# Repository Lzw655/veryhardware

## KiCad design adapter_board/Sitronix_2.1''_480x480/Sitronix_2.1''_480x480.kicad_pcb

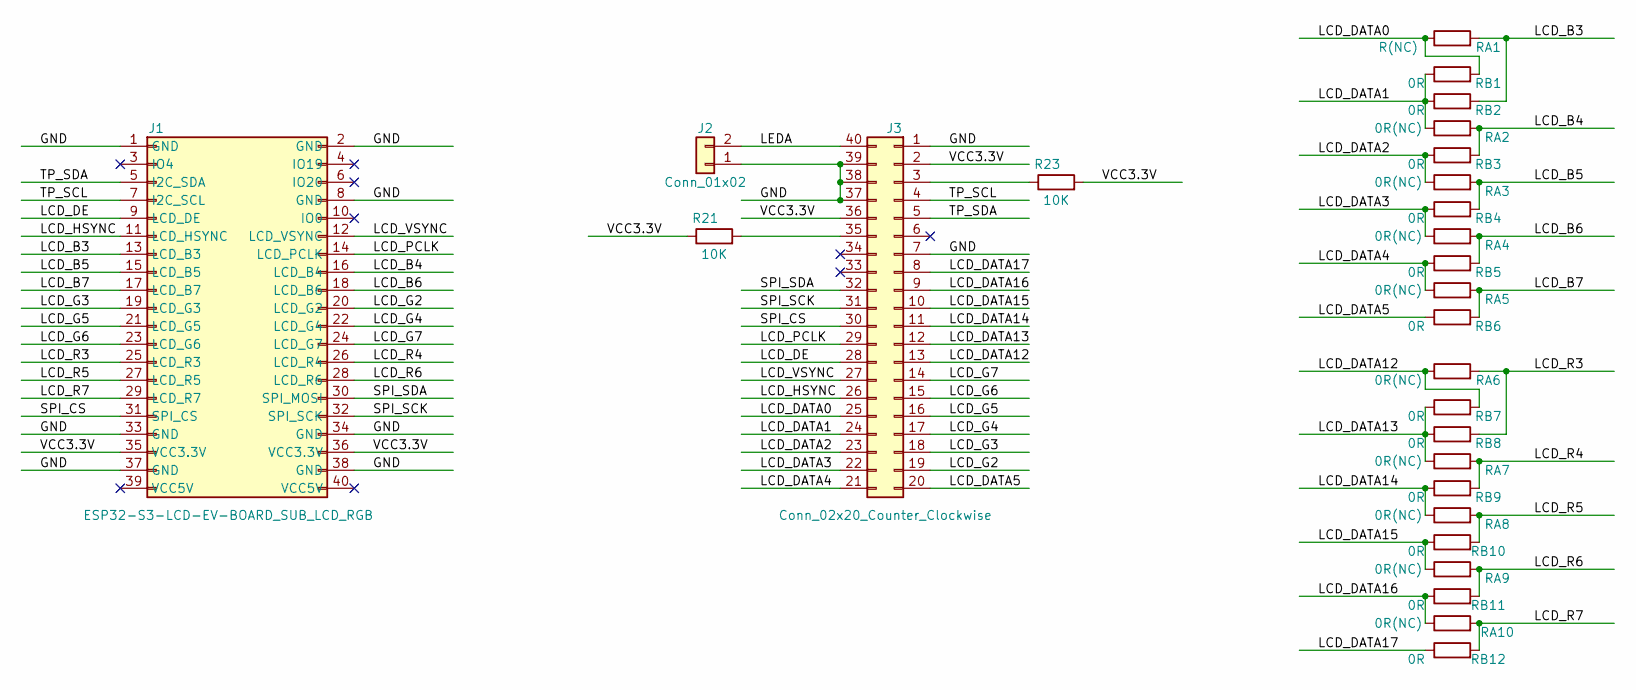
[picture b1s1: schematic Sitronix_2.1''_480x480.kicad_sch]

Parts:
J1: ESP32-S3-LCD-EV-BOARD_SUB_LCD_RGB
J2: Conn_01x02; PinHeader_1x02_P2.54mm_Vertical
J3: Conn_02x20_Counter_Clockwise; Hirose_FH12-40S-0.5SH_1x40-1MP_P0.50mm_Horizontal
R21, R23: 10K; R_0402_1005Metric
RA1, RA2, RA3, RA4, RA5, RA6, RA7, RA8, RA9, RA10: 0R(NC); R_0402_1005Metric
RB1, RB2, RB3, RB4, RB5, RB6, RB7, RB8, RB9, RB10, RB11, RB12: 0R; R_0402_1005Metric

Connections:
/GND: J1.1 (GND), J1.2 (GND), J1.8 (GND), J1.33 (GND), J1.34 (GND), J1.37 (GND), J1.38 (GND), J2.1, J3.1, J3.7, J3.37, J3.38, J3.39, J3.MP
/LCD_B3: J1.13 (LCD_B3), RA1.2, RB2.2
/LCD_B4: J1.16 (LCD_B4), RA2.2, RB3.2
/LCD_B5: J1.15 (LCD_B5), RA3.2, RB4.2
/LCD_B6: J1.18 (LCD_B6), RA4.2, RB5.2
/LCD_B7: J1.17 (LCD_B7), RA5.2, RB6.2
/LCD_DATA0: J3.25, RA1.1, RB1.2
/LCD_DATA1: J3.24, RA2.1, RB1.1, RB2.1
/LCD_DATA2: J3.23, RA3.1, RB3.1
/LCD_DATA3: J3.22, RA4.1, RB4.1
/LCD_DATA4: J3.21, RA5.1, RB5.1
/LCD_DATA5: J3.20, RB6.1
/LCD_DATA12: J3.13, RA6.1, RB7.2
/LCD_DATA13: J3.12, RA7.1, RB7.1, RB8.1
/LCD_DATA14: J3.11, RA8.1, RB9.1
/LCD_DATA15: J3.10, RA9.1, RB10.1
/LCD_DATA16: J3.9, RA10.1, RB11.1
/LCD_DATA17: J3.8, RB12.1
/LCD_DE: J1.9 (LCD_DE), J3.28
/LCD_G2: J1.20 (LCD_G2), J3.19
/LCD_G3: J1.19 (LCD_G3), J3.18
/LCD_G4: J1.22 (LCD_G4), J3.17
/LCD_G5: J1.21 (LCD_G5), J3.16
/LCD_G6: J1.23 (LCD_G6), J3.15
/LCD_G7: J1.24 (LCD_G7), J3.14
/LCD_HSYNC: J1.11 (LCD_HSYNC), J3.26
/LCD_PCLK: J1.14 (LCD_PCLK), J3.29
/LCD_R3: J1.25 (LCD_R3), RA6.2, RB8.2
/LCD_R4: J1.26 (LCD_R4), RA7.2, RB9.2
/LCD_R5: J1.27 (LCD_R5), RA8.2, RB10.2
/LCD_R6: J1.28 (LCD_R6), RA9.2, RB11.2
/LCD_R7: J1.29 (LCD_R7), RA10.2, RB12.2
/LCD_VSYNC: J1.12 (LCD_VSYNC), J3.27
/LEDA: J2.2, J3.40
/SPI_CS: J1.31 (SPI_CS), J3.30
/SPI_SCK: J1.32 (SPI_SCK), J3.31
/SPI_SDA: J1.30 (SPI_MOSI), J3.32
/TP_SCL: J1.7 (I2C_SCL), J3.4
/TP_SDA: J1.5 (I2C_SDA), J3.5
/VCC3.3V: J1.35 (VCC3.3V), J1.36 (VCC3.3V), J3.2, J3.36, R21.1, R23.2
unnamed: J3.3, R23.1
unnamed: J3.35, R21.2

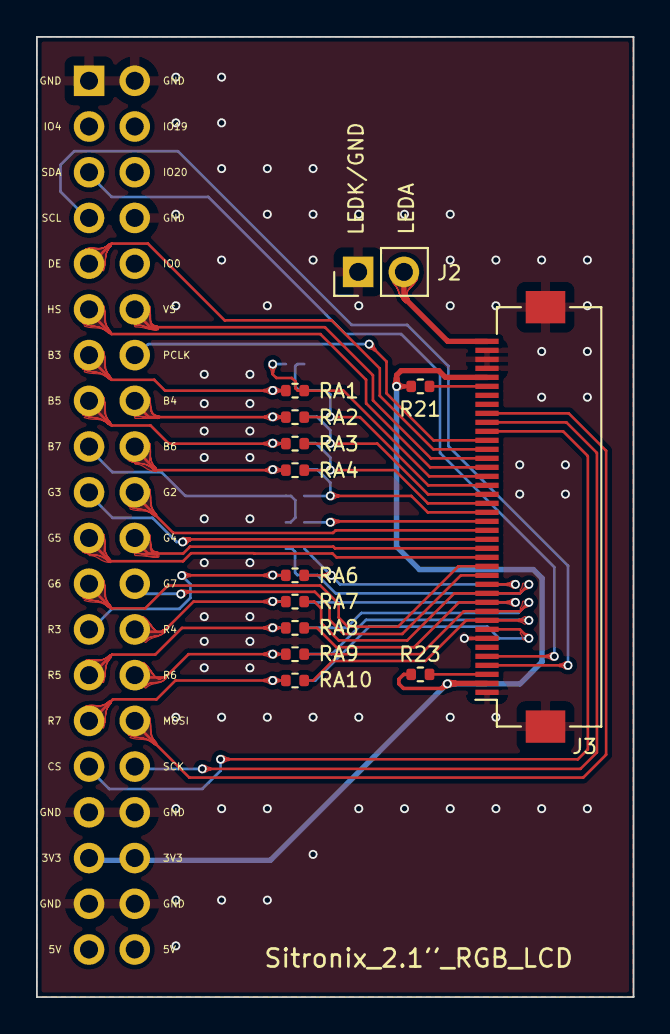
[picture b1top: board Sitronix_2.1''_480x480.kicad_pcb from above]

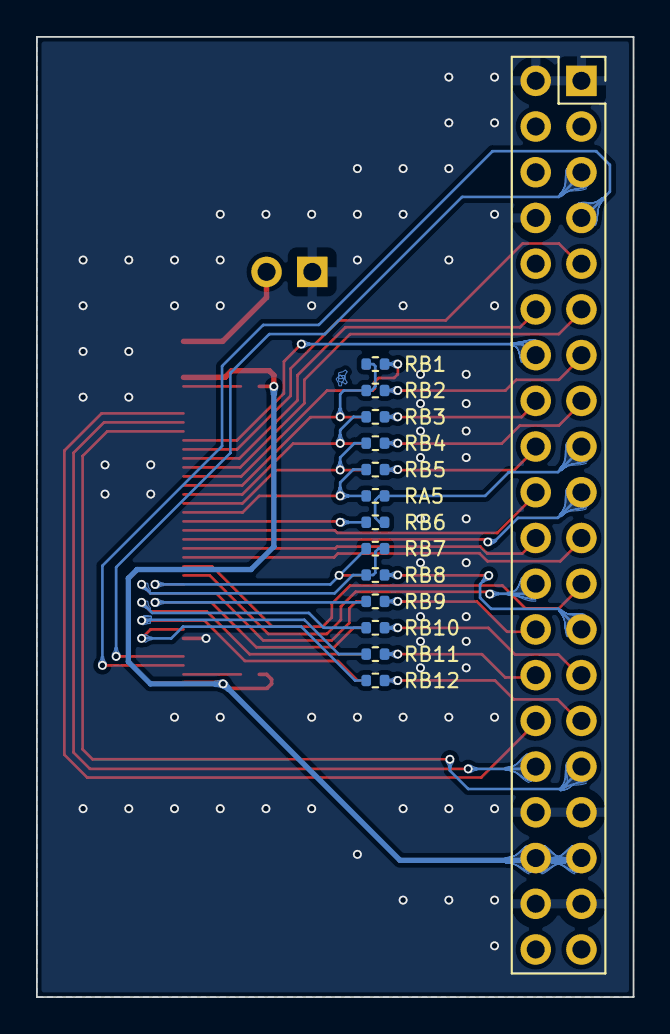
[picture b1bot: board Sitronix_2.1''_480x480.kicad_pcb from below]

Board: 2 copper layers, 33.1 x 53.3 mm, 27 parts (13 on the bottom side), 42 nets.

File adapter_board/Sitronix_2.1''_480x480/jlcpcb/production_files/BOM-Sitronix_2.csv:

Comment,Designator,Footprint,LCSC
ESP32-S3-LCD-EV-BOARD_SUB_LCD_RGB,J1,ESP32-S3-LCD-EV-BOARD_SUB_LCD_RGB,
0R(NC),RA10,R_0402_1005Metric,
10K,R23,R_0402_1005Metric,
0R(NC),RA8,R_0402_1005Metric,
R(NC),RA1,R_0402_1005Metric,
Conn_01x02,J2,PinHeader_1x02_P2.54mm_Vertical,
0R(NC),RA7,R_0402_1005Metric,
10K,R21,R_0402_1005Metric,
0R(NC),RA9,R_0402_1005Metric,
Conn_02x20_Counter_Clockwise,J3,Hirose_FH12-40S-0.5SH_1x40-1MP_P0.50mm_Horizontal,
0R(NC),RA4,R_0402_1005Metric,
0R(NC),RA2,R_0402_1005Metric,
0R(NC),RA3,R_0402_1005Metric,
0R(NC),RA6,R_0402_1005Metric,
0R,RB7,R_0402_1005Metric,
0R,RB2,R_0402_1005Metric,
0R,RB1,R_0402_1005Metric,
0R,RB9,R_0402_1005Metric,
0R,RB5,R_0402_1005Metric,
0R,RB12,R_0402_1005Metric,
0R,RB4,R_0402_1005Metric,
0R,RB8,R_0402_1005Metric,
0R,RB6,R_0402_1005Metric,
0R(NC),RA5,R_0402_1005Metric,
0R,RB11,R_0402_1005Metric,
0R,RB10,R_0402_1005Metric,
0R,RB3,R_0402_1005Metric,

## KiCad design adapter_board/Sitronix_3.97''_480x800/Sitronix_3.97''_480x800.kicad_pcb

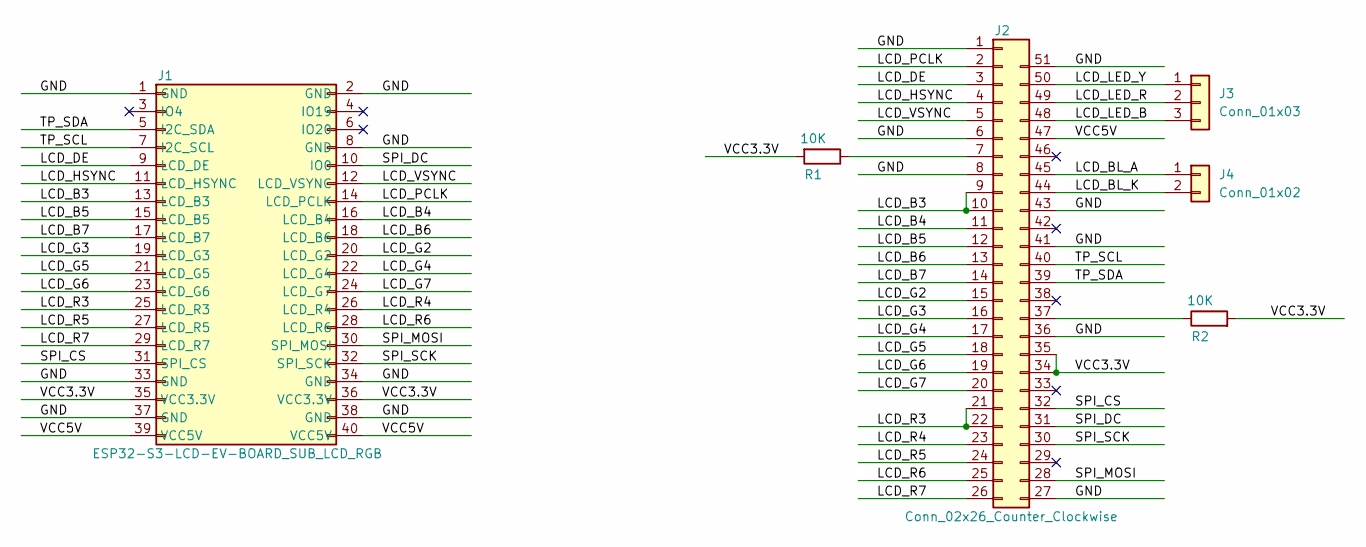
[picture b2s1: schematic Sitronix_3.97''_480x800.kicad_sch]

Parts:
J1: ESP32-S3-LCD-EV-BOARD_SUB_LCD_RGB; PinSocket_2x20_P2.54mm_Vertical
J2: Conn_02x26_Counter_Clockwise; Molex_502250-5191_2Rows-51Pins-1MP_P0.60mm_Horizontal
J3: Conn_01x03; PinHeader_1x03_P2.54mm_Vertical
J4: Conn_01x02; PinHeader_1x02_P2.54mm_Vertical
R1, R2: 10K; R_0603_1608Metric

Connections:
/GND: J1.1 (GND), J1.2 (GND), J1.8 (GND), J1.33 (GND), J1.34 (GND), J1.37 (GND), J1.38 (GND), J2.1, J2.6, J2.8, J2.27, J2.36, J2.41, J2.43, J2.51
/LCD_B3: J1.13 (LCD_B3), J2.9, J2.10
/LCD_B4: J1.16 (LCD_B4), J2.11
/LCD_B5: J1.15 (LCD_B5), J2.12
/LCD_B6: J1.18 (LCD_B6), J2.13
/LCD_B7: J1.17 (LCD_B7), J2.14
/LCD_BL_A: J2.45, J4.1
/LCD_BL_K: J2.44, J4.2
/LCD_DE: J1.9 (LCD_DE), J2.3
/LCD_G2: J1.20 (LCD_G2), J2.15
/LCD_G3: J1.19 (LCD_G3), J2.16
/LCD_G4: J1.22 (LCD_G4), J2.17
/LCD_G5: J1.21 (LCD_G5), J2.18
/LCD_G6: J1.23 (LCD_G6), J2.19
/LCD_G7: J1.24 (LCD_G7), J2.20
/LCD_HSYNC: J1.11 (LCD_HSYNC), J2.4
/LCD_LED_B: J2.48, J3.3
/LCD_LED_R: J2.49, J3.2
/LCD_LED_Y: J2.50, J3.1
/LCD_PCLK: J1.14 (LCD_PCLK), J2.2
/LCD_R3: J1.25 (LCD_R3), J2.21, J2.22
/LCD_R4: J1.26 (LCD_R4), J2.23
/LCD_R5: J1.27 (LCD_R5), J2.24
/LCD_R6: J1.28 (LCD_R6), J2.25
/LCD_R7: J1.29 (LCD_R7), J2.26
/LCD_VSYNC: J1.12 (LCD_VSYNC), J2.5
/SPI_CS: J1.31 (SPI_CS), J2.32
/SPI_DC: J1.10 (IO0), J2.31
/SPI_MOSI: J1.30 (SPI_MOSI), J2.28
/SPI_SCK: J1.32 (SPI_SCK), J2.30
/TP_SCL: J1.7 (I2C_SCL), J2.40
/TP_SDA: J1.5 (I2C_SDA), J2.39
/VCC3.3V: J1.35 (VCC3.3V), J1.36 (VCC3.3V), J2.34, J2.35, R1.2, R2.2
/VCC5V: J1.39 (VCC5V), J1.40 (VCC5V), J2.47
unnamed: J2.7, R1.1
unnamed: J2.37, R2.1

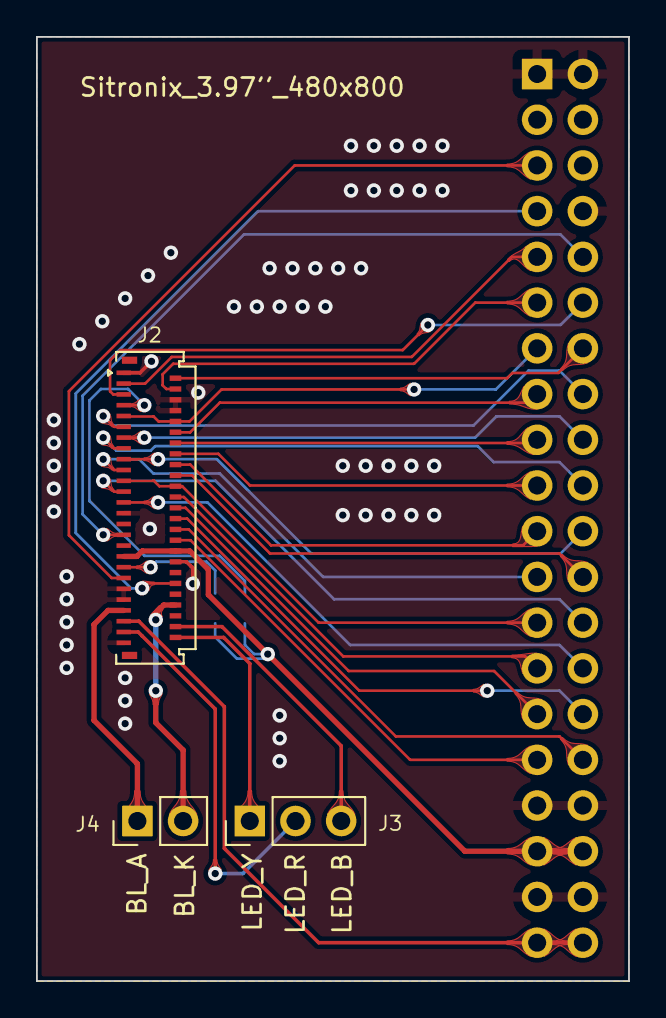
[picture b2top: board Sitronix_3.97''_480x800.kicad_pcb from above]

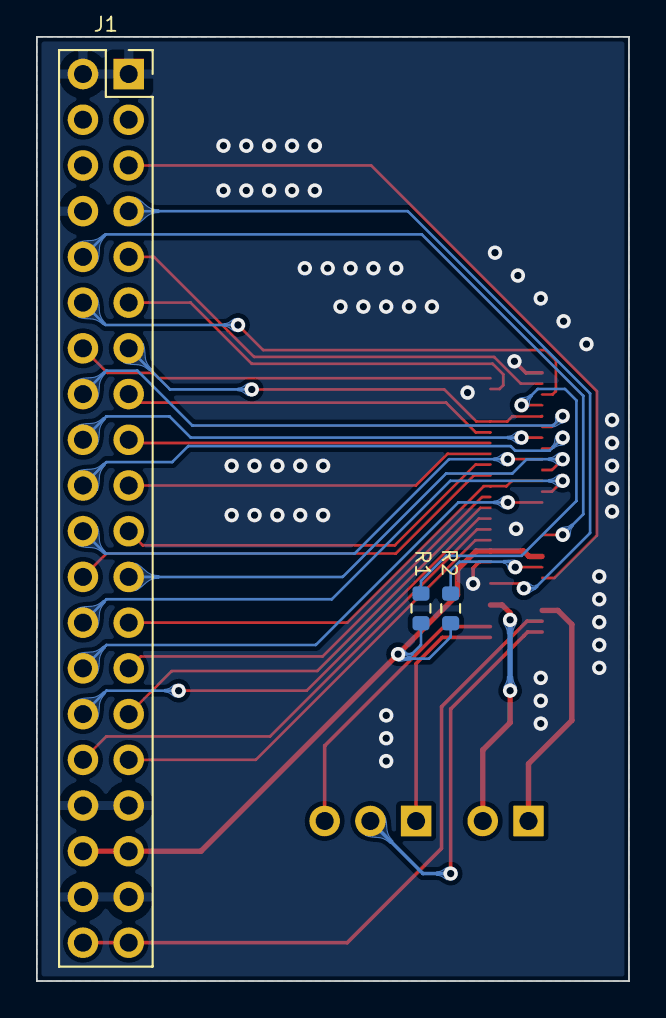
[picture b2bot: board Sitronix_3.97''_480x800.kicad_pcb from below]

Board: 2 copper layers, 32.9 x 52.5 mm, 6 parts (3 on the bottom side), 36 nets.

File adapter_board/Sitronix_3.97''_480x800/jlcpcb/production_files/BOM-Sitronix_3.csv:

Comment,Designator,Footprint,LCSC
Conn_02x26_Counter_Clockwise,J2,Molex_502250-5191_2Rows-51Pins-1MP_P0.60mm_Horizontal,
10K,R2,R_0603_1608Metric,
Conn_01x02,J4,PinHeader_1x02_P2.54mm_Vertical,
Conn_01x03,J3,PinHeader_1x03_P2.54mm_Vertical,
10K,R1,R_0603_1608Metric,
ESP32-S3-LCD-EV-BOARD_SUB_LCD_RGB,J1,PinSocket_2x20_P2.54mm_Vertical,

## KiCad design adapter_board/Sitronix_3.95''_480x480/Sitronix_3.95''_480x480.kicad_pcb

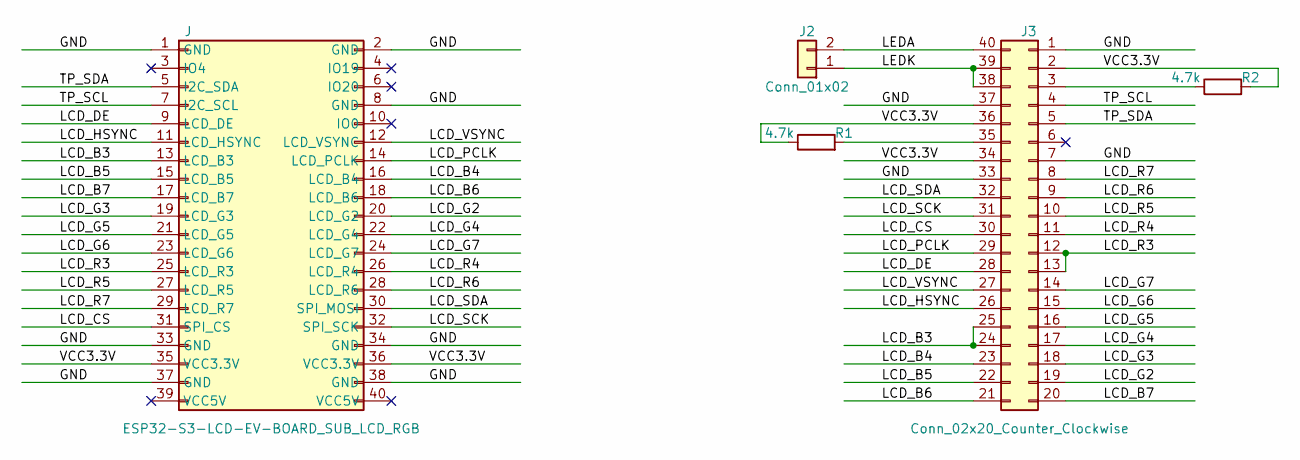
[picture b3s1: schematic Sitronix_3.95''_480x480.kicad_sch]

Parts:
J: ESP32-S3-LCD-EV-BOARD_SUB_LCD_RGB; PinSocket_2x20_P2.54mm_Vertical
J2: Conn_01x02
J3: Conn_02x20_Counter_Clockwise
R1: 4.7k
R2: 4.7k; R_0603_1608Metric

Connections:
/GND: J.1 (GND), J.2 (GND), J.8 (GND), J.33 (GND), J.34 (GND), J.37 (GND), J.38 (GND), J3.1, J3.7, J3.33, J3.37, J3.MP
/LCD_B3: J.13 (LCD_B3), J3.24, J3.25
/LCD_B4: J.16 (LCD_B4), J3.23
/LCD_B5: J.15 (LCD_B5), J3.22
/LCD_B6: J.18 (LCD_B6), J3.21
/LCD_B7: J.17 (LCD_B7), J3.20
/LCD_CS: J.31 (SPI_CS), J3.30
/LCD_DE: J.9 (LCD_DE), J3.28
/LCD_G2: J.20 (LCD_G2), J3.19
/LCD_G3: J.19 (LCD_G3), J3.18
/LCD_G4: J.22 (LCD_G4), J3.17
/LCD_G5: J.21 (LCD_G5), J3.16
/LCD_G6: J.23 (LCD_G6), J3.15
/LCD_G7: J.24 (LCD_G7), J3.14
/LCD_HSYNC: J.11 (LCD_HSYNC), J3.26
/LCD_PCLK: J.14 (LCD_PCLK), J3.29
/LCD_R3: J.25 (LCD_R3), J3.12, J3.13
/LCD_R4: J.26 (LCD_R4), J3.11
/LCD_R5: J.27 (LCD_R5), J3.10
/LCD_R6: J.28 (LCD_R6), J3.9
/LCD_R7: J.29 (LCD_R7), J3.8
/LCD_SCK: J.32 (SPI_SCK), J3.31
/LCD_SDA: J.30 (SPI_MOSI), J3.32
/LCD_VSYNC: J.12 (LCD_VSYNC), J3.27
/LEDA: J2.2, J3.40
/LEDK: J2.1, J3.38, J3.39
/TP_SCL: J.7 (I2C_SCL), J3.4
/TP_SDA: J.5 (I2C_SDA), J3.5
/VCC3.3V: J.35 (VCC3.3V), J.36 (VCC3.3V), J3.2, J3.34, J3.36, R1.1, R2.2
unnamed: J3.35, R1.2
unnamed: J3.3, R2.1

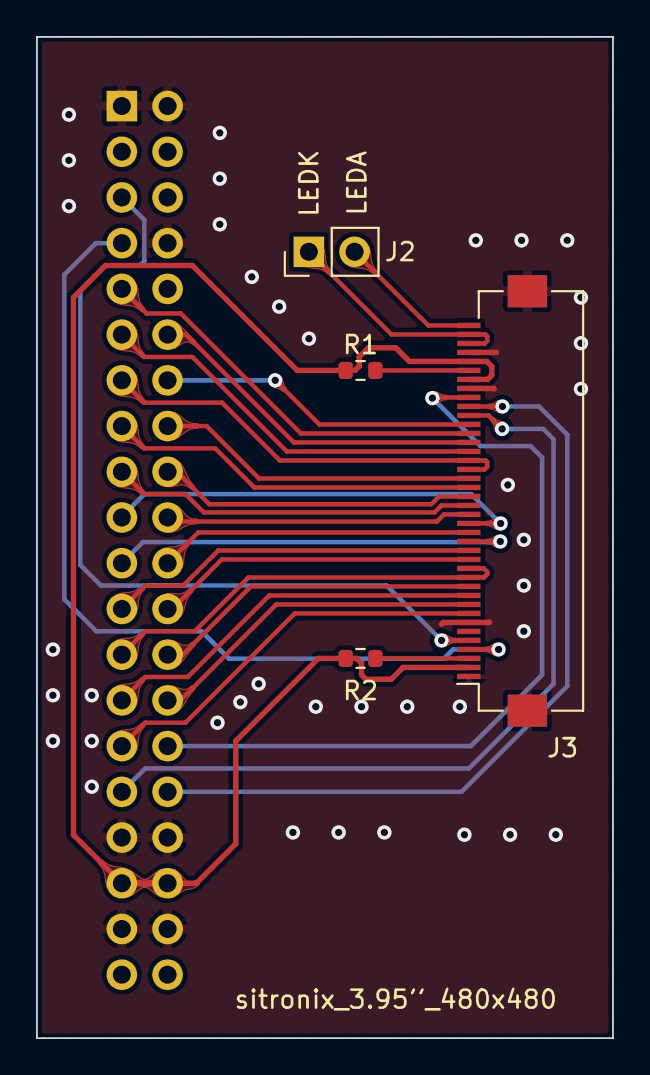
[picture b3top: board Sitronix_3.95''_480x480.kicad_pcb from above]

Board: 2 copper layers, 32.0 x 55.6 mm, 5 parts (1 on the bottom side), 31 nets.

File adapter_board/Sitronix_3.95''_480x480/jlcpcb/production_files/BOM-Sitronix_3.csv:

Comment,Designator,Footprint,LCSC
Conn_02x20_Counter_Clockwise,J3,Hirose_FH12-40S-0.5SH_1x40-1MP_P0.50mm_Horizontal,
4.7k,R2,R_0603_1608Metric,
4.7k,R1,R_0603_1608Metric,
Conn_01x02,J2,PinHeader_1x02_P2.54mm_Vertical,
ESP32-S3-LCD-EV-BOARD_SUB_LCD_RGB,J1,PinSocket_2x20_P2.54mm_Vertical,

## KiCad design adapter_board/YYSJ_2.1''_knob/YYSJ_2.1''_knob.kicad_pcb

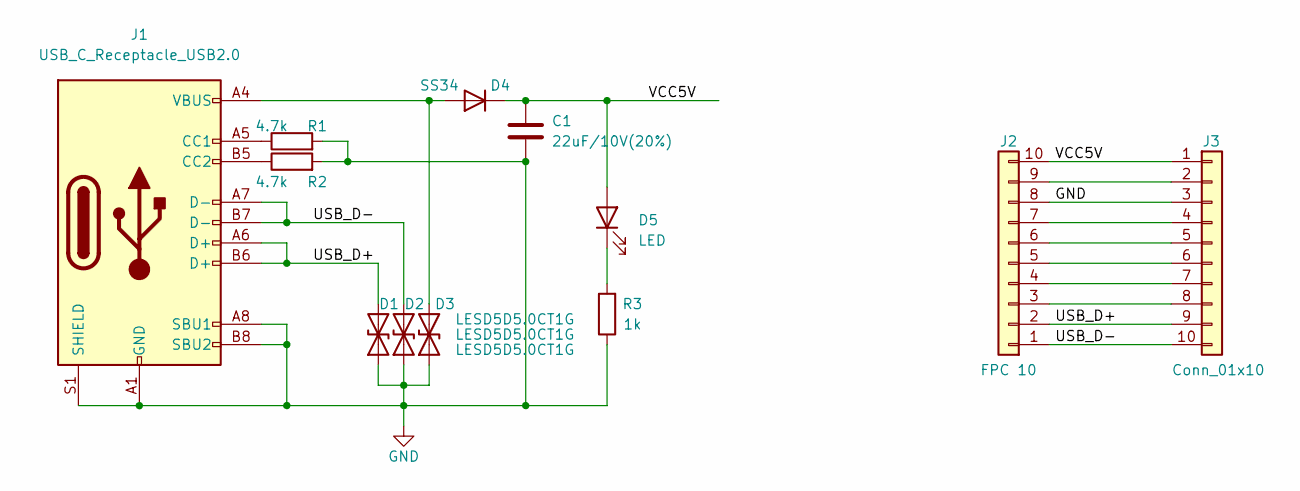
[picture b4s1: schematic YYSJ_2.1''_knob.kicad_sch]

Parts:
C1: 22uF/10V(20%); C_0603_1608Metric
D1, D2, D3: LESD5D5.0CT1G; D_SOD-523
D4: SS34; D_SMA
D5: LED; LED_0603_1608Metric
J1: USB_C_Receptacle_USB2.0; USB_C_Receptacle_HRO_TYPE-C-31-M-12
J2: FPC 10; Hirose_FH12-10S-0.5SH_1x10-1MP_P0.50mm_Horizontal
J3: Conn_01x10; PinHeader_1x10_P2.54mm_Horizontal
R1, R2: 4.7k; R_0603_1608Metric
R3: 1k; R_0603_1608Metric

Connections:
/USB_D+: D1.2 (A2), J1.A6 (D+), J1.B6 (D+), J2.2, J3.9
/USB_D-: D2.2 (A2), J1.A7 (D-), J1.B7 (D-), J2.1, J3.10
/VCC5V: C1.1, D4.1 (K), D5.2 (A), J2.10, J3.1
GND: C1.2, D1.1 (A1), D2.1 (A1), D3.1 (A1), J1.A1 (GND), J1.A8 (SBU1), J1.A12 (GND), J1.B1 (GND), J1.B8 (SBU2), J1.B12 (GND), J1.S1 (SHIELD), J2.8, J3.3, R1.2, R2.2, R3.1
unnamed: D3.2 (A2), D4.2 (A), J1.A4 (VBUS), J1.A9 (VBUS), J1.B4 (VBUS), J1.B9 (VBUS)
unnamed: D5.1 (K), R3.2
unnamed: J1.A5 (CC1), R1.1
unnamed: J1.B5 (CC2), R2.1
unnamed: J2.3, J3.8
unnamed: J2.4, J3.7
unnamed: J2.5, J3.6
unnamed: J2.6, J3.5
unnamed: J2.7, J3.4
unnamed: J2.9, J3.2

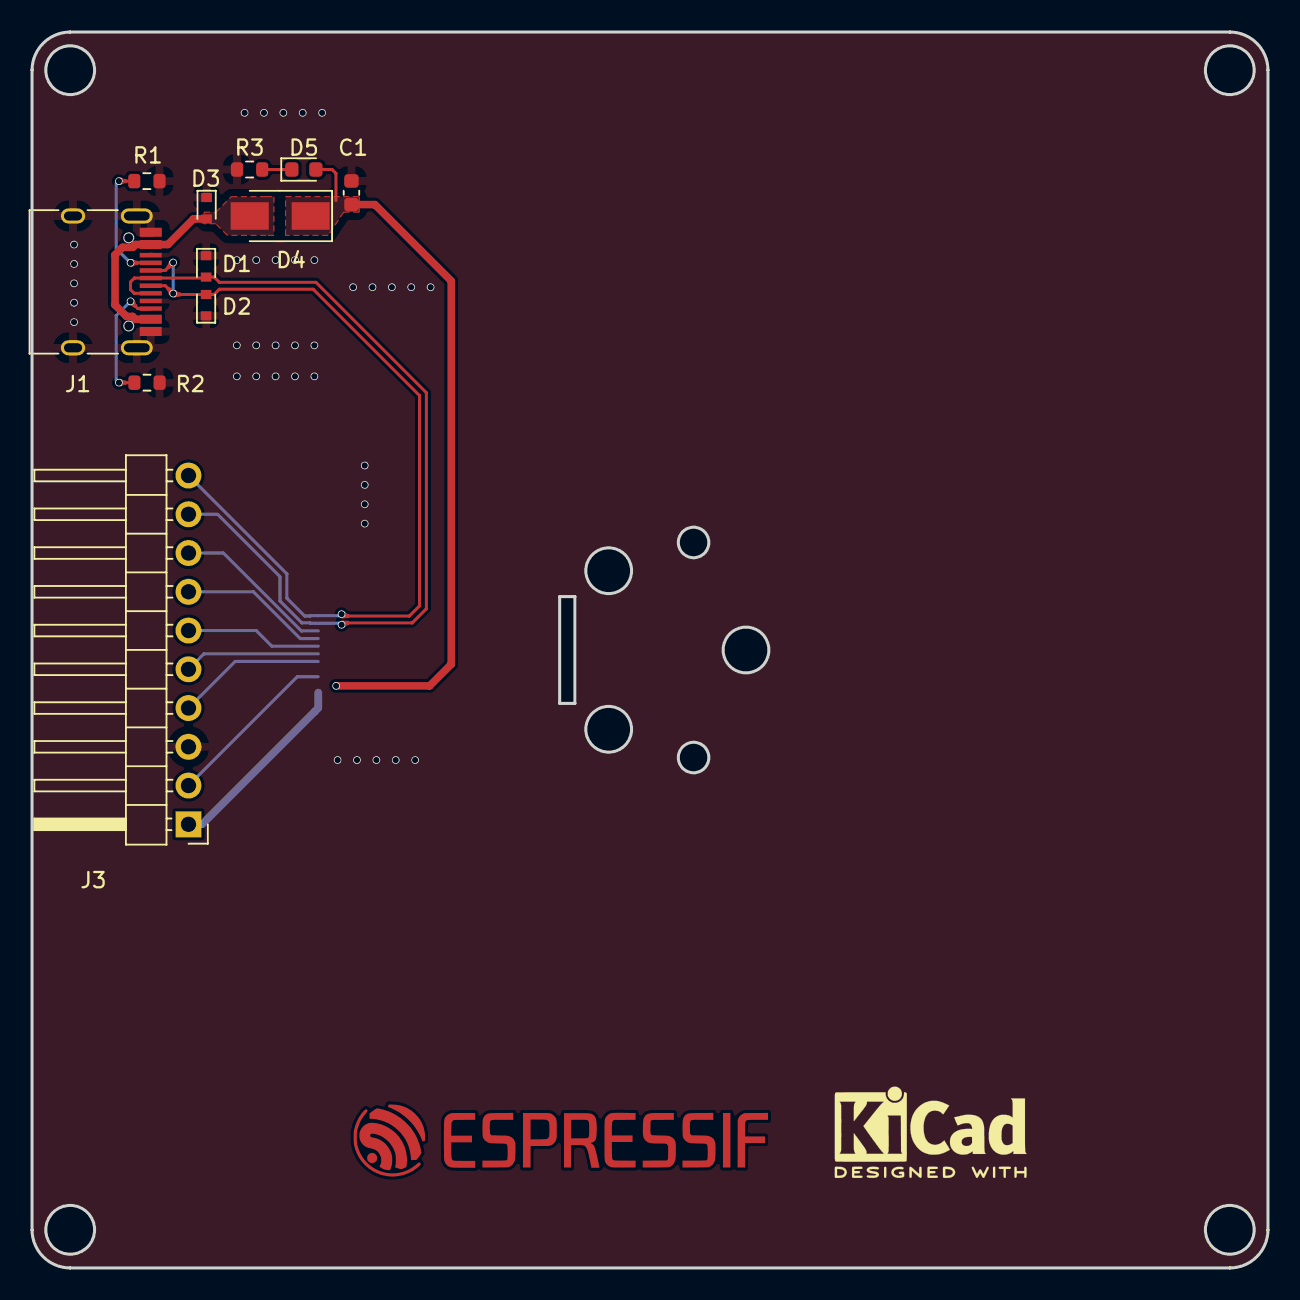
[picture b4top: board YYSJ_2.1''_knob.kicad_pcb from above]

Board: 2 copper layers, 81.0 x 81.0 mm, 12 parts (1 on the bottom side), 14 nets.

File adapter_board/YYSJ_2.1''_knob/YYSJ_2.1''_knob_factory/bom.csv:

Designator,Footprint,Quantity,Value,LCSC Part #
J3,PinHeader_1x10_P2.54mm_Horizontal,1,Conn_01x10,
R3,R_0603_1608Metric,1,1k,
D2,D_SOD-523,1,LESD5D5.0CT1G,
D3,D_SOD-523,1,LESD5D5.0CT1G,
D1,D_SOD-523,1,LESD5D5.0CT1G,
J1,USB_C_Receptacle_HRO_TYPE-C-31-M-12,1,USB_C_Receptacle_USB2.0,
D5,LED_0603_1608Metric,1,LED,
R1,R_0603_1608Metric,1,4.7k,
D4,D_SMA,1,SS34,
C1,C_0603_1608Metric,1,22uF/10V(20%),
R2,R_0603_1608Metric,1,4.7k,
J2,Hirose_FH12-10S-0.5SH_1x10-1MP_P0.50mm_Horizontal,1,FPC 10,

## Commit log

2022-11-12 adapter_board: add YYSJ_2.1''_knob
2022-11-12 adapter_board.YYSJ_2.1''knob: finish electric
2022-11-13 adapter_board.YYSJ_2.1''knob: finish
2022-11-13 adapter_board.ZDYZ_7''knob: finish
2022-11-14 remove backup
2022-11-21 adapter_board.sitronix_3.97''_480x800: finish
2022-11-21 adapter_board.sitronix_3.95''_480x480: finish
2022-11-30 adapter_board.sitronix_3.97''_800x480: modify
2022-12-03 adapter_board: add Sitronix_2.1''_480x480
2022-12-25 Sitronix_2.1''_480x480: modify pcb
2022-12-25 generate sch pdf
